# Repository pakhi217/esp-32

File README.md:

# ⚡ ESP32 KiCad PCB Design

A custom PCB designed using **KiCad** for an **ESP32-based embedded system**. This project focuses on creating a clean, modular, and reliable hardware design suitable for IoT, embedded systems, and electronics applications.

---

## 📖 Overview

This repository contains the complete KiCad project files required to view, edit, and manufacture the PCB. The design is centered around the ESP32 microcontroller and follows standard PCB design practices for efficient routing and easy prototyping.

---

## ✨ Features

* ESP32-based PCB design
* Designed using KiCad
* Organized schematic and PCB layout
* Ready for further customization and fabrication
* Suitable for embedded systems and IoT projects

---

## 🛠 Software Used

* **KiCad** – Schematic capture and PCB layout

---

## 📂 Project Structure

```text
├── Schematic Files
├── PCB Layout Files
├── Footprints
├── Symbols
├── Design Rules
└── README.md
```

---

## 🚀 Getting Started

1. Clone this repository.
2. Open the project in **KiCad**.
3. Review the schematic and PCB layout.
4. Modify the design if required.
5. Generate Gerber files for PCB manufacturing.

---

## 📌 Applications

* IoT Devices
* Embedded Systems
* Wireless Communication Projects
* Electronics Prototyping
* ESP32 Development

---

## 🤝 Contributions

Contributions, suggestions, and improvements are welcome. Feel free to fork the repository and submit a pull request.

---

## 📄 License

This project is available for educational and personal use. Add an open-source license if you plan to distribute or collaborate publicly.

---

## 👩‍💻 Author

**PAKHI SAXENA**
**B.Tech Electronics & Communication Engineering (ECE) Student**

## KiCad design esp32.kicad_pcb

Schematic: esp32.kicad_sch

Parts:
C1: 22 uf; CP_EIA-3528-12_Kemet-T
C2: 22uf; CP_EIA-3528-12_Kemet-T
C3: 22uf; C_0805_2012Metric
C4, C6: 100nf; C_0805_2012Metric
C5: 1uf; C_0805_2012Metric
D1: LED; LED_0805_2012Metric
D2: WS2812B-2020; LED_WS2812B-2020_PLCC4_2.0x2.0mm
J1: USB_C_Receptacle_USB2.0_14P; USB_C_Receptacle_GCT_USB4105-xx-A_16P_TopMnt_Horizontal
J2, J3: Conn_01x20_Pin; PinHeader_1x20_P2.54mm_Vertical
R1: 2k; R_0805_2012Metric
R2, R3: 10k; R_0805_2012Metric
R4: 100R; R_0805_2012Metric
R5, R6: 5.1k; R_0805_2012Metric
SW1, SW2: SW_Push; SW_Push_SPST_NO_Alps_SKRK
U1: ESP32-S3-WROOM-1
U2: AMS1117-3.3; SOT-223-3_TabPin2

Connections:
+3V3: C1.1, C3.1, C4.1, D2.4 (VDD), J2.1, R2.1, R3.1, U1.2 (3V3), U2.2 (VO)
+5V: C2.1, J1.A4 (VBUS), J1.A9 (VBUS), J1.B4 (VBUS), J1.B9 (VBUS), R1.1, U2.3 (VI)
BOOT: J2.4, R3.2, R4.1, U1.27 (IO0)
D+: J1.A6 (D+), J1.B6 (D+), U1.14 (USB_D+)
D-: J1.A7 (D-), J1.B7 (D-), U1.13 (USB_D-)
EN: C5.1, C6.1, J2.3, R2.2, SW1.1, U1.3 (EN)
GND: C1.2, C2.2, C3.2, C4.2, C5.2, C6.2, D1.1 (K), D2.2 (VSS), J1.A1 (GND), J1.A12 (GND), J1.B1 (GND), J1.B12 (GND), J1.S1 (SHIELD), J2.2, J3.16, J3.17, J3.19, R5.2, R6.2, SW1.2, SW2.2, U1.1 (GND), U1.40 (GND), U1.41 (GND), U2.1 (GND)
I047: U1.24 (IO47)
IO1: J2.5, U1.39 (IO1)
IO2: J2.6, U1.38 (IO2)
IO3: J2.7, U1.15 (IO3)
IO4: J2.8, U1.4 (IO4)
IO5: J2.9, U1.5 (IO5)
IO6: J2.10, U1.6 (IO6)
IO7: J2.11, U1.7 (IO7)
IO8: J2.12, U1.12 (IO8)
IO9: J2.13, U1.17 (IO9)
IO10: J2.14, U1.18 (IO10)
IO11: J2.15, U1.19 (IO11)
IO12: J2.16, U1.20 (IO12)
IO13: J2.17, U1.21 (IO13)
IO14: J2.18, U1.22 (IO14)
IO15: J2.19, U1.8 (IO15)
IO16: J2.20, U1.9 (IO16)
IO17: J3.14, U1.10 (IO17)
IO18: J3.15, U1.11 (IO18)
IO23: J3.13, U1.23 (IO21)
IO35: J3.12, U1.28 (IO35)
IO36: J3.11, U1.29 (IO36)
IO37: J3.10, U1.30 (IO37)
IO38: J3.9, U1.31 (IO38)
IO39: J3.8, U1.32 (IO39)
IO40: J3.7, U1.33 (IO40)
IO41: J3.6, U1.34 (IO41)
IO42: J3.5, U1.35 (IO42)
IO45: J3.4, U1.26 (IO45)
IO46: J3.3, U1.16 (IO46)
IO47: J3.2
IO48: D2.3 (DIN), J3.1, U1.25 (IO48)
unnamed: D1.2 (A), R1.2
unnamed: J1.A5 (CC1), R6.1
unnamed: J1.B5 (CC2), R5.1
unnamed: R4.2, SW2.1
RX: U1.36 (RXD0)
TX: J3.18, U1.37 (TXD0)

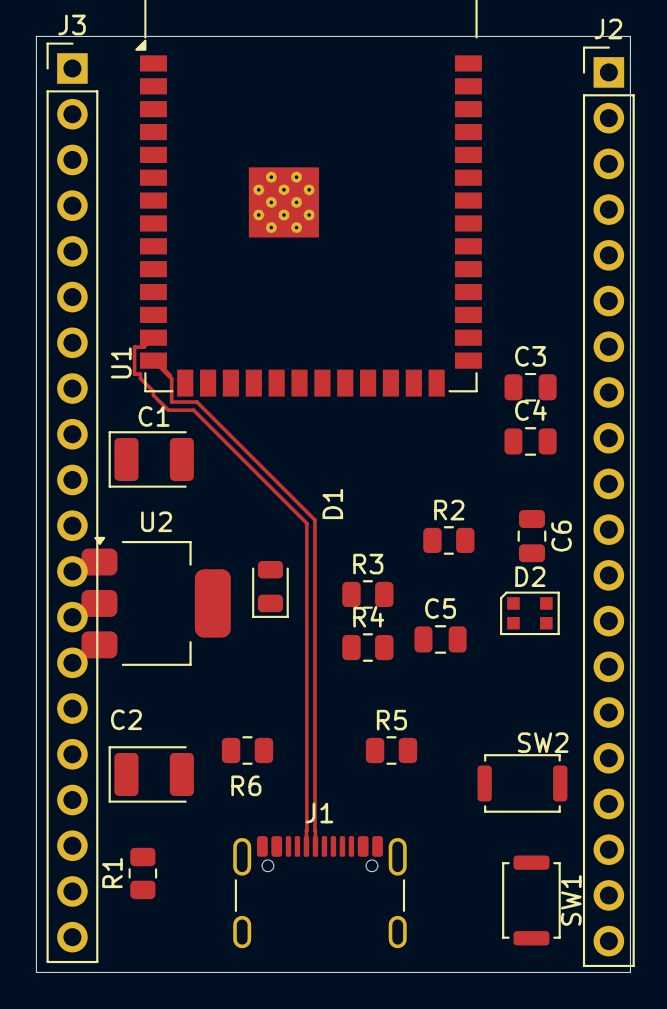
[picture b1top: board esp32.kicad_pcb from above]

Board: 2 copper layers, 33.0 x 52.0 mm, 21 parts (0 on the bottom side), 42 nets.
